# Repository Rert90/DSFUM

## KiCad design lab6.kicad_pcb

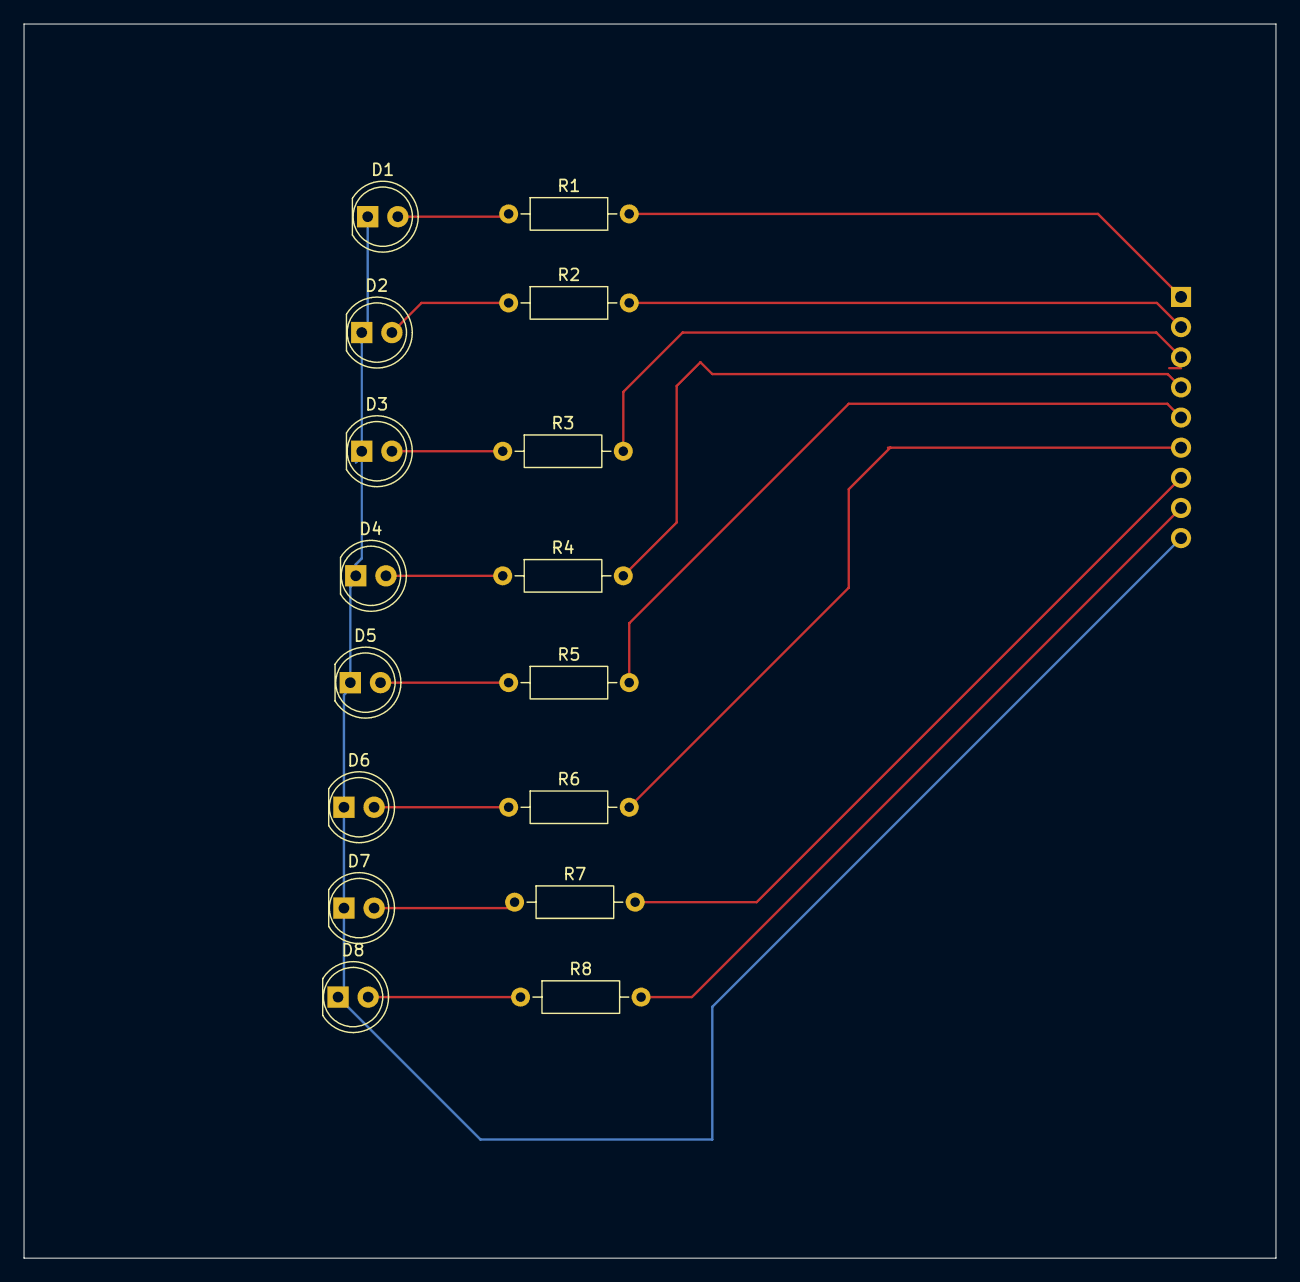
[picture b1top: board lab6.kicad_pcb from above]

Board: 2 copper layers, 105.5 x 104.0 mm, 17 parts (1 on the bottom side), 17 nets.

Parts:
D1, D2, D3, D4, D5, D6, D7, D8: LED; LED_D5.0mm
J1: Conn_01x09; PinHeader_1x09_P2.54mm_Vertical
R1, R2, R3, R4, R5, R6, R7, R8: R; R_Axial_DIN0207_L6.3mm_D2.5mm_P10.16mm_Horizontal

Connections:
GND: D1.1 (K), D2.1 (K), D3.1 (K), D4.1 (K), D5.1 (K), D6.1 (K), D7.1 (K), D8.1 (K), J1.9
unnamed: D1.2 (A), R1.1
unnamed: D2.2 (A), R2.1
unnamed: D3.2 (A), R3.1
unnamed: D4.2 (A), R4.1
unnamed: D5.2 (A), R5.1
unnamed: D6.2 (A), R6.1
unnamed: D7.2 (A), R7.1
unnamed: D8.2 (A), R8.1
unnamed: J1.1, R1.2
unnamed: J1.2, R2.2
unnamed: J1.3, R3.2
unnamed: J1.4, R4.2
unnamed: J1.5, R5.2
unnamed: J1.6, R6.2
unnamed: J1.7, R7.2
unnamed: J1.8, R8.2
